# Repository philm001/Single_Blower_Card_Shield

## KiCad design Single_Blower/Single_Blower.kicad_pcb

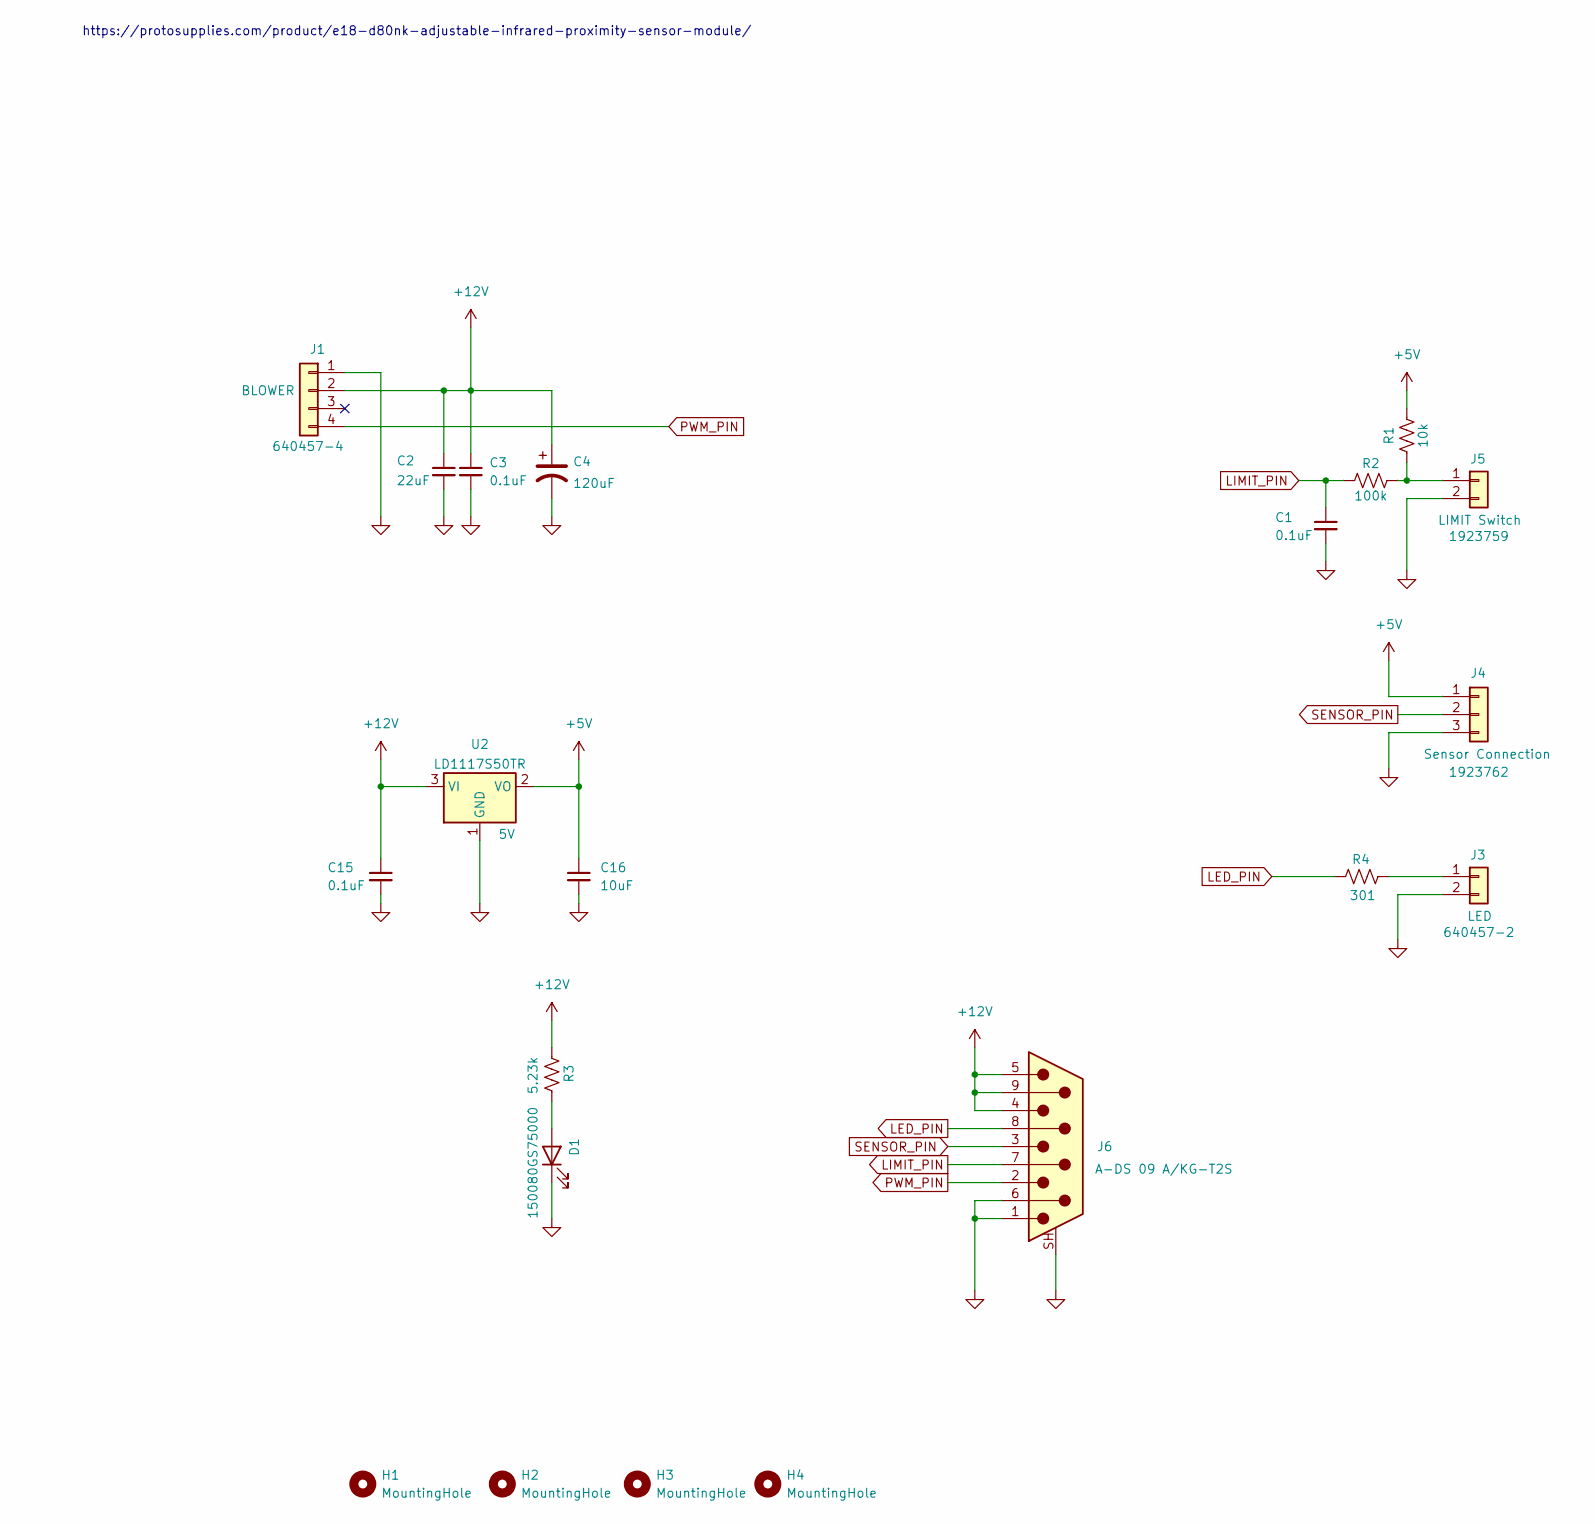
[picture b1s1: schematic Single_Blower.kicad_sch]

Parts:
C1: 0.1uF; C_0805_2012Metric; Mfg. PN CL21B104KBCNNNC
C2: 22uF; C_0805_2012Metric; Mfg. PN CL21A226MAYNNNE
C3, C15: 0.1uF; C_0805_2012Metric; Mfg. PN Samsung Electro-Mechanics
C4: 120uF; CP_Elec_6.3x5.8; Mfg. PN APXG200ARA121MF61G
C16: 10uF; C_0805_2012Metric; Mfg. PN Samsung Electro-Mechanics
D1: PWR; LED_0805_2012Metric; Mfg. PN 150080GS75000
H1, H2, H3, H4: MountingHole; MountingHole_3.2mm_M3_DIN965
J1: BLOWER; TE_640457-4; Mfg. PN 640457-4
J3: LED; TE_640457-2; Mfg. PN 640457-2
J4: Sensor Connection; PHOENIX_1923762; Mfg. PN 1923762
J5: LIMIT Switch; PHOENIX_1923759; Mfg. PN 1923759
J6: DE9_Pins_MountingHoles; ASSMANN_A-DS_09_A_KG-T2S; Mfg. PN A-DS 09 A/KG-T2S
R1: 10k; R_0805_2012Metric; Mfg. PN RMCF0805FT10K0
R2: 100k; R_0805_2012Metric; Mfg. PN RMCF0805FG100K
R3: 5.23k; R_0805_2012Metric; Mfg. PN RMCF0805FT5K23
R4: 301; R_0805_2012Metric; Mfg. PN RMCF0805FT301R
U2: 5V; SOT-223-3_TabPin2; Mfg. PN LD1117S50TR

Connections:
+5V: C16.1, J4.1, R1.1, U2.2 (VO)
+12V: C2.1, C3.1, C4.1, C15.1, J1.2, J6.4, J6.5, J6.9, R3.1, U2.3 (VI)
GND: C1.2, C2.2, C3.2, C4.2, C15.2, C16.2, D1.1 (K), J1.1, J3.2, J4.3, J5.2, J6.1, J6.6, J6.SH (PAD), U2.1 (GND)
LED_PIN: J6.8, R4.1
LIMIT_PIN: C1.1, J6.7, R2.1
unnamed: D1.2 (A), R3.2
unnamed: J3.1, R4.2
unnamed: J5.1, R1.2, R2.2
PWM_PIN: J1.4, J6.2
SENSOR_PIN: J4.2, J6.3

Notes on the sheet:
https://protosupplies.com/product/e18-d80nk-adjustable-infrared-proximity-sensor-module/

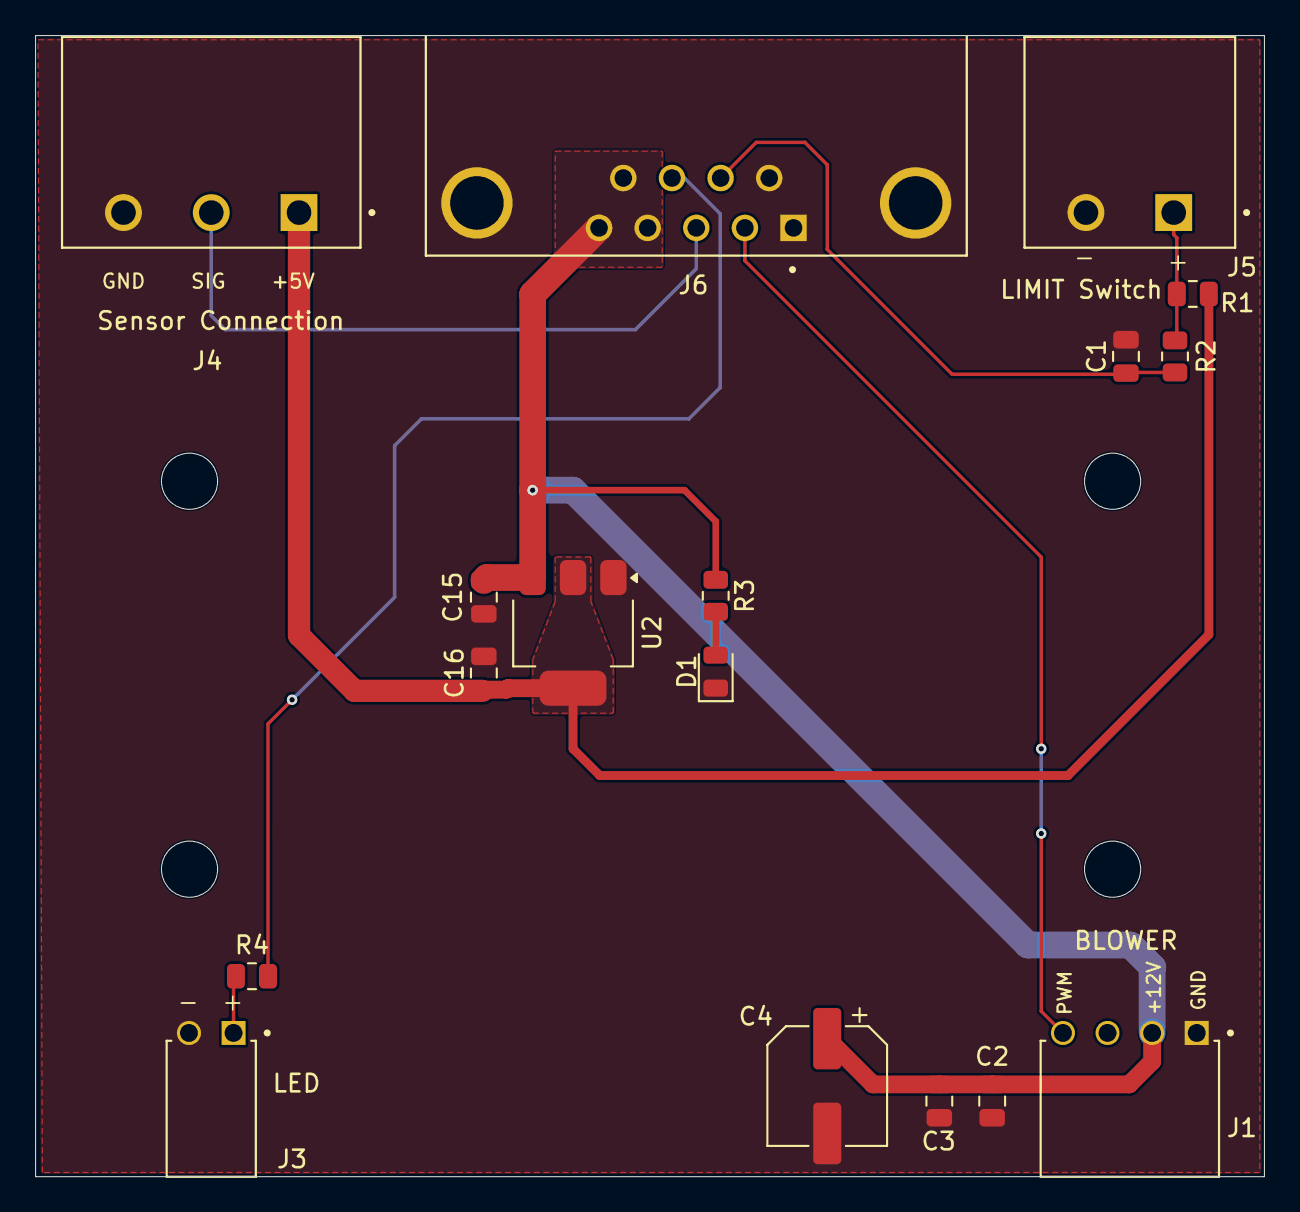
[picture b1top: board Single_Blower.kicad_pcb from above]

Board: 2 copper layers, 70.0 x 65.0 mm, 21 parts (0 on the bottom side), 10 nets.

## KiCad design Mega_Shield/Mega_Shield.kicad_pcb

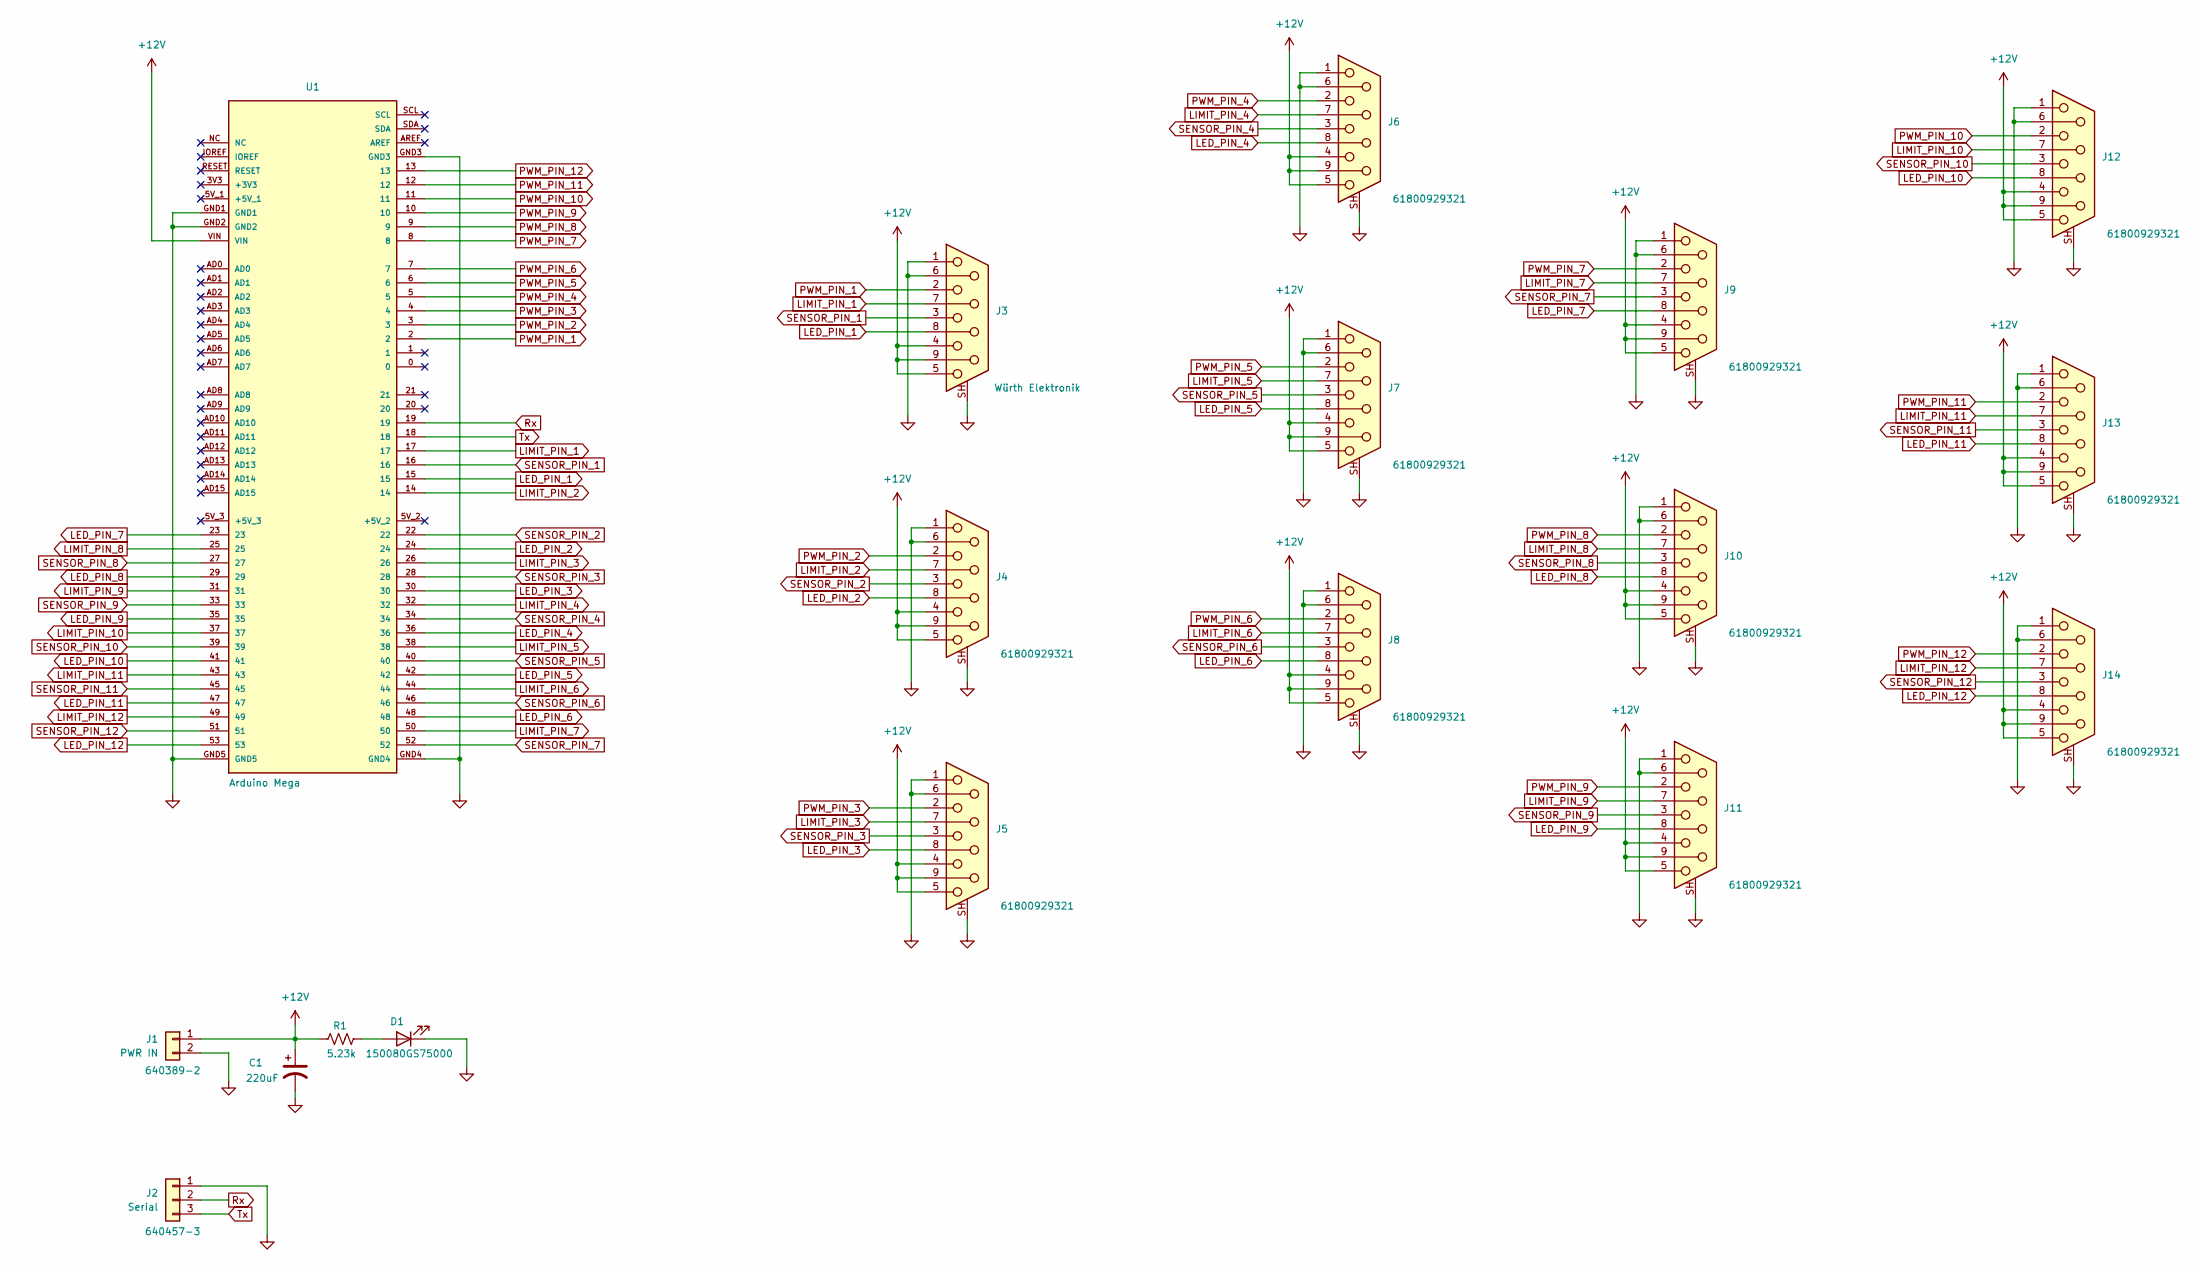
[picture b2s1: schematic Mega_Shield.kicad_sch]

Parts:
C1: 220uF; CP_Elec_8x10; Mfg. PN Nichicon
D1: PWR; LED_0805_2012Metric; Mfg. PN 150080GS75000
J1: PWR IN; TE_640389-2; Mfg. PN 640389-2
J2: Serial; TE_640457-3; Mfg. PN 640457-3
J3: DE9_Socket_MountingHoles; 61800929321; Mfg. PN Würth Elektronik
J4, J5, J6, J7, J8, J9, J10, J11, J12, J13, J14: DE9_Socket_MountingHoles; 61800929321; Mfg. PN 61800929321
R1: 5.23k; R_0805_2012Metric; Mfg. PN RMCF0805FT5K23
U1: Arduino Mega; ARDUINO_A000067

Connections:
+12V: C1.1, J1.1, J3.4, J3.5, J3.9, J4.4, J4.5, J4.9, J5.4, J5.5, J5.9, J6.4, J6.5, J6.9, J7.4, J7.5, J7.9, J8.4, J8.5, J8.9, J9.4, J9.5, J9.9, J10.4, J10.5, J10.9, J11.4, J11.5, J11.9, J12.4, J12.5, J12.9, J13.4, J13.5, J13.9, J14.4, J14.5, J14.9, R1.1, U1.VIN
GND: C1.2, D1.1 (K), J1.2, J2.1, J3.1, J3.6, J3.SH (PAD), J4.1, J4.6, J4.SH (PAD), J5.1, J5.6, J5.SH (PAD), J6.1, J6.6, J6.SH (PAD), J7.1, J7.6, J7.SH (PAD), J8.1, J8.6, J8.SH (PAD), J9.1, J9.6, J9.SH (PAD), J10.1, J10.6, J10.SH (PAD), J11.1, J11.6, J11.SH (PAD), J12.1, J12.6, J12.SH (PAD), J13.1, J13.6, J13.SH (PAD), J14.1, J14.6, J14.SH (PAD), U1.GND1, U1.GND2, U1.GND3, U1.GND4, U1.GND5
LED_PIN_1: J3.8, U1.15
LED_PIN_2: J4.8, U1.24
LED_PIN_3: J5.8, U1.30
LED_PIN_4: J6.8, U1.36
LED_PIN_5: J7.8, U1.42
LED_PIN_6: J8.8, U1.48
LED_PIN_7: J9.8, U1.23
LED_PIN_8: J10.8, U1.29
LED_PIN_9: J11.8, U1.35
LED_PIN_10: J12.8, U1.41
LED_PIN_11: J13.8, U1.47
LED_PIN_12: J14.8, U1.53
LIMIT_PIN_1: J3.7, U1.17
LIMIT_PIN_2: J4.7, U1.14
LIMIT_PIN_3: J5.7, U1.26
LIMIT_PIN_4: J6.7, U1.32
LIMIT_PIN_5: J7.7, U1.38
LIMIT_PIN_6: J8.7, U1.44
LIMIT_PIN_7: J9.7, U1.50
LIMIT_PIN_8: J10.7, U1.25
LIMIT_PIN_9: J11.7, U1.31
LIMIT_PIN_10: J12.7, U1.37
LIMIT_PIN_11: J13.7, U1.43
LIMIT_PIN_12: J14.7, U1.49
unnamed: D1.2 (A), R1.2
PWM_PIN_1: J3.2, U1.2
PWM_PIN_2: J4.2, U1.3
PWM_PIN_3: J5.2, U1.4
PWM_PIN_4: J6.2, U1.5
PWM_PIN_5: J7.2, U1.6
PWM_PIN_6: J8.2, U1.7
PWM_PIN_7: J9.2, U1.8
PWM_PIN_8: J10.2, U1.9
PWM_PIN_9: J11.2, U1.10
PWM_PIN_10: J12.2, U1.11
PWM_PIN_11: J13.2, U1.12
PWM_PIN_12: J14.2, U1.13
Rx: J2.2, U1.19
SENSOR_PIN_1: J3.3, U1.16
SENSOR_PIN_2: J4.3, U1.22
SENSOR_PIN_3: J5.3, U1.28
SENSOR_PIN_4: J6.3, U1.34
SENSOR_PIN_5: J7.3, U1.40
SENSOR_PIN_6: J8.3, U1.46
SENSOR_PIN_7: J9.3, U1.52
SENSOR_PIN_8: J10.3, U1.27
SENSOR_PIN_9: J11.3, U1.33
SENSOR_PIN_10: J12.3, U1.39
SENSOR_PIN_11: J13.3, U1.45
SENSOR_PIN_12: J14.3, U1.51
Tx: J2.3, U1.18

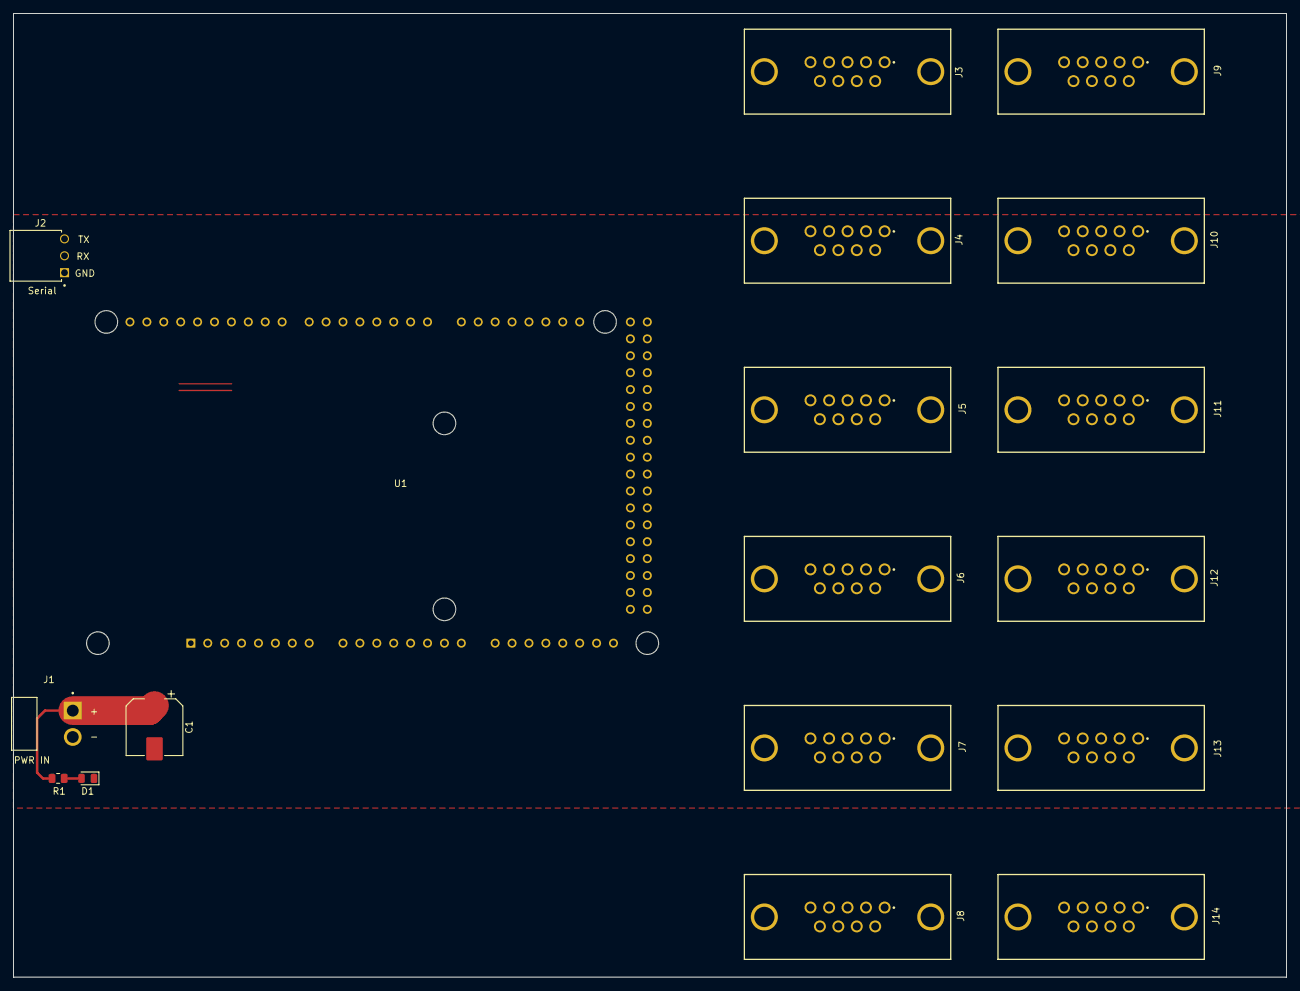
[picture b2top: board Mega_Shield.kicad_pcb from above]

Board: 2 copper layers, 191.3 x 144.8 mm, 18 parts (0 on the bottom side), 53 nets.
